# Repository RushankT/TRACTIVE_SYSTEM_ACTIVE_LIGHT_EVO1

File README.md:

# TRACTIVE_SYSTEM_ACTIVE_LIGHT_EVO1

## Overview

This repository contains the finalized KiCad schematic design for the **Tractive System Active Light (TSAL)** circuit, developed for our Formula Student Electric Vehicle project. The TSAL is a critical safety component used to indicate the presence of high voltage in the tractive system when the vehicle is powered on.

## Project Details

- **Project Name**: TSAL Final Design
- **Team**: Zuura Formula Racing
- **Engineer**: Rushank Talwar, EV Powertrain Lead
- **Tool Used**: KiCad (Recommended version: 6.x or newer)
- **Date**: July 2025

## Functionality

The TSAL circuit complies with Formula Student Electric rules and includes:
- A high-brightness red LED indicator visible from 3 meters.
- Blinking at ≥ 1 Hz when TS voltage > 60 VDC.
- Green Light Turns on when TS voltage < 60 VDC.
- Isolation and safety using optocouplers and fail-safe design.
- Powered by a reliable low-voltage source (e.g., 12V DC).

## File Structure

- `TSAL_final.kicad_sch`: Main schematic file for the TSAL circuit.
- (Optional) Future files: `TSAL_final.kicad_pcb`, BOM, gerber files.

## Relevant Rules

EV4.10 Tractive System Active Light

EV4.10.1 The vehicles must include a single TSAL that must indicate the TS status. The TSAL must
not perform any other functions. A TSAL with multiple LEDs in one housing is allowed.

EV4.10.2 The TSAL itself must have a red light, flashing continuously with a frequency between 2 Hz
and 5 Hz and a duty cycle of 50%, active if and only if the LVS is active and the voltage
across any DC-link capacitor exceeds
• 60VDC or 50VACRMS
• Half the nominal TS voltage
whichever is lower.

EV4.10.3 The TSAL itself must have a green light, continuously on, active if and only if the LVS is
active and ALL of the following conditions are true:
• All AIRs are opened.
• The pre-charge relay, see EV5.7.2, is opened.
• The voltage at the vehicle side of the AIRs inside the TSAC does not exceed 60VDC
or 50VACRMS.

EV4.10.4 The mentioned voltage detection must be performed inside the respective TS enclosure.

EV4.10.5 The mentioned states of the relays (opened/closed) are the actual mechanical states. The
mechanical state can differ from the intentional state, i.e. if a relay is stuck. Any circuitry
detecting the mechanical state must meet EV5.6.2.

EV4.10.6 The voltage detection circuit of the red light and the relay state and voltage detection circuit
of the green light must be independent. Any plausibility check between both lights is not
allowed. A TSAL state with both lights simultaneously active might occur and must not be
prevented.

EV4.10.7 The TSAL must:
• Be located lower than the highest point of the main hoop and including the mounting
within the rollover protection envelope, see T1.1.15.
• Be no lower than 75mm from the highest point of the main hoop.
• Not be able to contact the driver’s helmet in any circumstances.

EV4.10.8 The entire illuminated surface of the TSAL must be clearly visible:
• Except for angles less than 10° which are blocked by the main hoop.
• From a point 1:60m vertically from ground level, within 3m horizontal radius from
the TSAL.
• In direct sunlight.

EV4.10.9 The TSAL and all needed circuitry must be hard-wired electronics. Software control is not
permitted.

EV4.10.10 A green indicator light in the cockpit that is easily visible even in bright sunlight and clearly
marked with “TS off” must light up if TSAL green light is on, see EV4.10.3.

EV4.10.11 Signals influencing the TSAL and the indicator according to EV4.10.10 are SCS, see T11.9.
The individual safe state of each of the TSAL lights is off. The TSAL has an active indication
of the absence of failures (continuous green illumination) and thus the red light must not be
illuminated for a visible check, see T11.9.5.

EV4.10.12 The TSAL’s red light voltage detection circuit, see EV4.10.2, does not need to detect an
open circuit, as required by T11.9, when no voltage is present. A plausibility check must not
be implemented.

EV4.10.13 The TSAL’s green light relay state detection circuit, see EV4.10.3, does not need to detect an
open circuit, as required by T11.9, when the intentional state of the used (auxiliary) contact
is opened. A plausibility check using the intentional relay state must be implemented in a
way that the TSAL’s green light stays off after the open circuit is detectable.

EV4.10.14 The TSAL’s green light voltage detection circuit, see EV4.10.3, does not need to detect an
open circuit, as required by T11.9, when no voltage is present. A plausibility check using
the intentional relay states must be implemented in a way that the TSAL’s green light stays
off after the open circuit of the accumulator voltage detection circuit is detectable.

EV4.10.15 The latching required by EV4.10.13 and EV4.10.14 must not be triggered during normal
operation conditions and must only be reset by power cycling the LVS.

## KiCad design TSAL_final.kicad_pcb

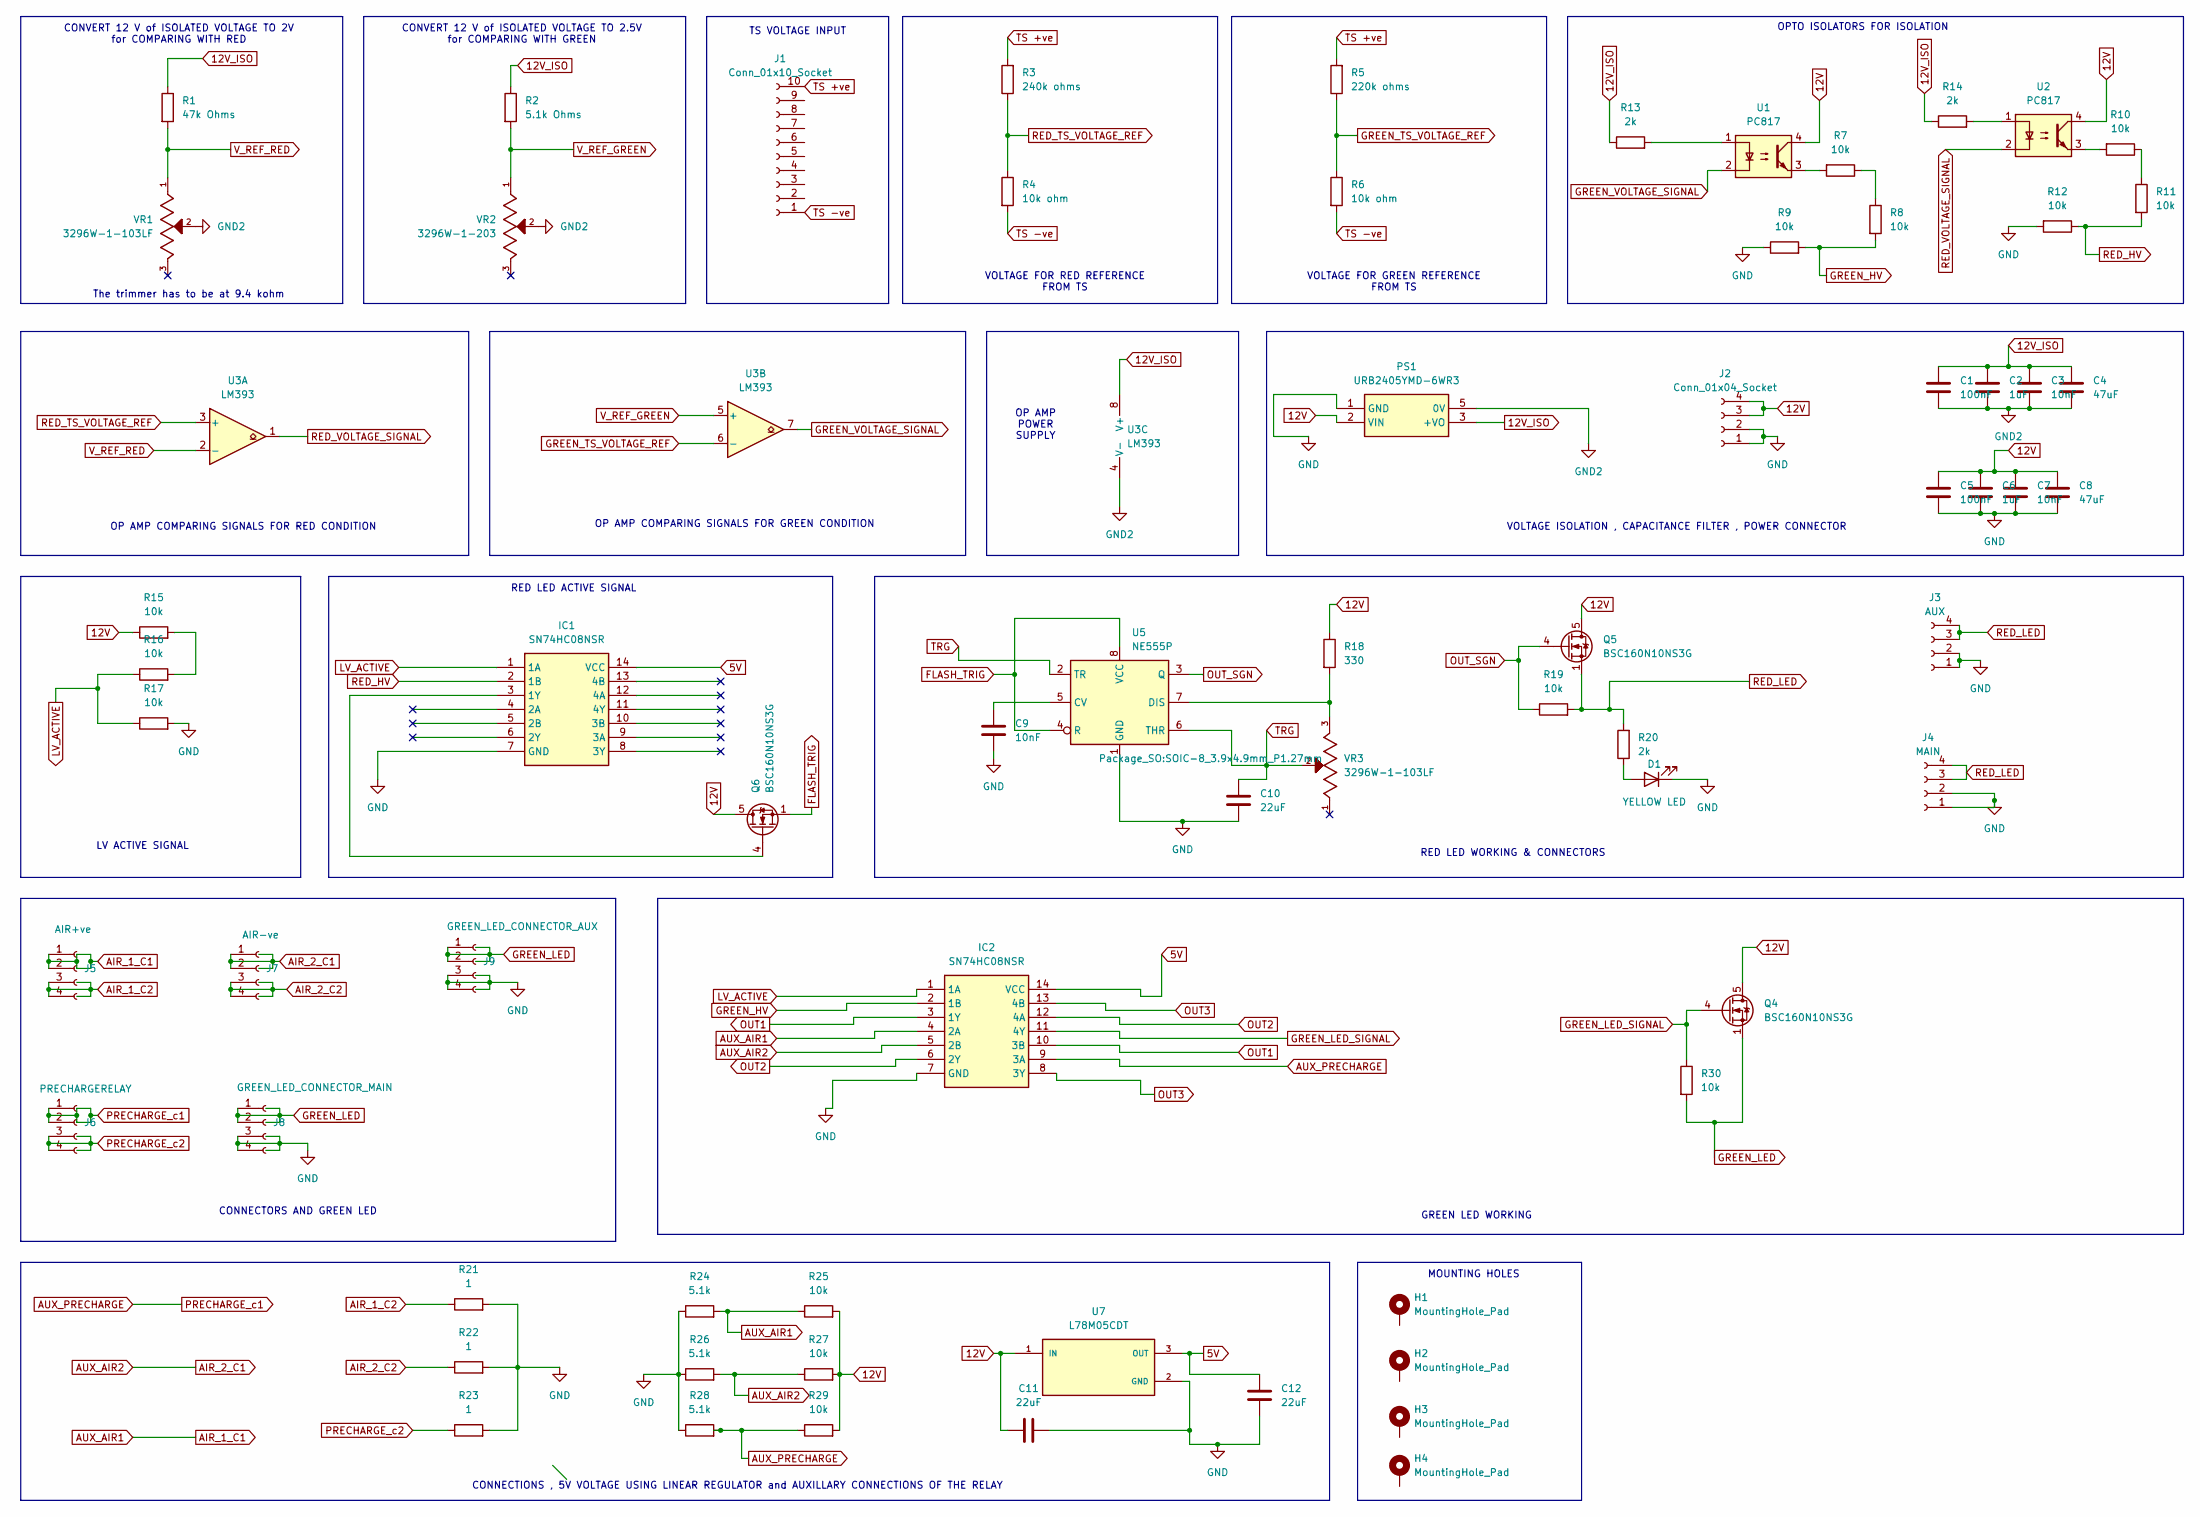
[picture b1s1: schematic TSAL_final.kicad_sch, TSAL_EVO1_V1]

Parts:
C1, C5: 100nF; C_0805_2012Metric_Pad1.18x1.45mm_HandSolder
C2, C6: 1uF; C_0805_2012Metric_Pad1.18x1.45mm_HandSolder
C3, C7, C9: 10nF; C_0805_2012Metric_Pad1.18x1.45mm_HandSolder
C4, C8: 47uF; C_0805_2012Metric_Pad1.18x1.45mm_HandSolder
C10, C11, C12: 22uF; C_0805_2012Metric_Pad1.18x1.45mm_HandSolder
D1: YELLOW LED; LED_0805_2012Metric_Pad1.15x1.40mm_HandSolder
H1, H2, H3, H4: MountingHole_Pad; MountingHole_4.3mm_M4_ISO7380_Pad_TopBottom
IC1, IC2: SN74HC08NSR; SOIC127P780X200-14N; Mouser Part Number 595-SN74HC08NSR
J1: Conn_01x10_Socket; JST_VH_B10P-VH-B_1x10_P3.96mm_Vertical
J2: Conn_01x04_Socket; JST_VH_B4P-VH-B_1x04_P3.96mm_Vertical
J3: AUX; JST_VH_B4P-VH-B_1x04_P3.96mm_Vertical
J4: MAIN; JST_VH_B4P-VH-B_1x04_P3.96mm_Vertical
J5: AIR+ve; JST_VH_B4P-VH-B_1x04_P3.96mm_Vertical
J6: PRECHARGERELAY; JST_VH_B4P-VH-B_1x04_P3.96mm_Vertical
J7: AIR-ve; JST_VH_B4P-VH-B_1x04_P3.96mm_Vertical
J8: GREEN_LED_CONNECTOR_MAIN; JST_VH_B4P-VH-B_1x04_P3.96mm_Vertical
J9: GREEN_LED_CONNECTOR_AUX; JST_VH_B4P-VH-B_1x04_P3.96mm_Vertical
PS1: URB2405YMD-6WR3; URB2405YMD6WR3; Manufacturer_Part_Number URB2405YMD-6WR3
Q4, Q5, Q6: BSC160N10NS3G; TDSON-8-1
R1: 47k Ohms; R_0805_2012Metric_Pad1.20x1.40mm_HandSolder
R2: 5.1k Ohms; R_0805_2012Metric_Pad1.20x1.40mm_HandSolder
R3: 240k ohms; R_2512_6332Metric_Pad1.40x3.35mm_HandSolder
R4, R6: 10k ohm; R_2512_6332Metric_Pad1.40x3.35mm_HandSolder
R5: 220k ohms; R_2512_6332Metric_Pad1.40x3.35mm_HandSolder
R7, R8, R9, R10, R11, R12, R15, R16, R17, R19, R25, R27, R29, R30: 10k; R_0805_2012Metric_Pad1.20x1.40mm_HandSolder
R13, R14, R20: 2k; R_0805_2012Metric_Pad1.20x1.40mm_HandSolder
R18: 330; R_0805_2012Metric_Pad1.20x1.40mm_HandSolder
R21, R22, R23: 1; R_0805_2012Metric_Pad1.20x1.40mm_HandSolder
R24, R26, R28: 5.1k; R_0805_2012Metric_Pad1.20x1.40mm_HandSolder
U1, U2: PC817; DIP-4_W7.62mm
U3: LM393; SO08
U5: NE555P; SOIC-8_3.9x4.9mm_P1.27mm
U7: L78M05CDT; VREG_L78M05CDT; PARTREV 24
VR1, VR3: 3296W-1-103LF; TRIM_3296W-1-103LF; PARTREV 05/16
VR2: 3296W-1-203; TRIM_3296W-1-203; PARTREV 05/16

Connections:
5V: C12.2, IC1.14 (VCC), IC2.14 (VCC), U7.3 (OUT)
12V: C5.1, C6.1, C7.1, C8.1, C11.1, J2.3, J2.4, PS1.2 (VIN), Q4.5 (D), Q5.5 (D), Q6.5 (D), R15.1, R18.1, R25.2, R27.2, R29.2, U1.4, U2.4, U7.1 (IN)
12V_ISO: C1.1, C2.1, C3.1, C4.1, PS1.3 (+VO), R1.1, R2.1, R13.1, R14.1, U3.8 (V+)
AIR_1_C1: IC2.4 (2A), J5.1, J5.2, R24.2, R25.1
AIR_1_C2: J5.3, J5.4, R21.1
AIR_2_C1: IC2.5 (2B), J7.1, J7.2, R26.2, R27.1
AIR_2_C2: J7.3, J7.4, R22.1
AUX_PRECHARGE: IC2.9 (3A), J6.1, J6.2, R28.2, R29.1
FLASH_TRIG: Q6.1 (S), Q6.2 (S), Q6.3 (S), U5.4 (R), U5.8 (VCC)
GND: C5.2, C6.2, C7.2, C8.2, C9.2, C10.2, C11.2, C12.1, D1.1 (K), IC1.7 (GND), IC2.7 (GND), J2.1, J2.2, J3.1, J3.2, J4.1, J4.2, J8.3, J8.4, J9.3, J9.4, PS1.1 (GND), R9.1, R12.2, R17.2, R21.2, R22.2, R23.2, R24.1, R26.1, R28.1, U5.1 (GND), U7.2 (GND)
GND2: C1.2, C2.2, C3.2, C4.2, PS1.5 (0V), U3.4 (V-), VR1.2, VR2.2
GREEN_HV: IC2.2 (1B), R8.2, R9.2
GREEN_LED: J8.1, J8.2, J9.1, J9.2, Q4.1 (S), Q4.2 (S), Q4.3 (S), R30.2
GREEN_LED_SIGNAL: IC2.11 (4Y), Q4.4 (G), R30.1
GREEN_TS_VOLTAGE_REF: R5.1, R6.1, U3.6 (-)
GREEN_VOLTAGE_SIGNAL: U1.2, U3.7
LV_ACTIVE: IC1.1 (1A), IC2.1 (1A), R16.1, R17.1
unnamed: D1.2 (A), R20.1
unnamed: IC1.3 (1Y), Q6.4 (G)
unnamed: R7.1, R8.1
unnamed: R7.2, U1.3
unnamed: R10.1, R11.1
unnamed: R10.2, U2.3
unnamed: R13.2, U1.1
unnamed: R14.2, U2.1
unnamed: R15.2, R16.2
unnamed: C9.1, U5.5 (CV)
unnamed: R18.2, U5.7 (DIS), VR3.3
OUT1: IC2.3 (1Y), IC2.10 (3B)
OUT2: IC2.6 (2Y), IC2.12 (4A)
OUT3: IC2.8 (3Y), IC2.13 (4B)
OUT_SGN: Q5.4 (G), R19.1, U5.3 (Q)
PRECHARGE_c2: J6.3, J6.4, R23.1
RED_HV: IC1.2 (1B), R11.2, R12.1
RED_LED: J3.3, J3.4, J4.3, J4.4, Q5.1 (S), Q5.2 (S), Q5.3 (S), R19.2, R20.2
RED_TS_VOLTAGE_REF: R3.1, R4.1, U3.3 (+)
RED_VOLTAGE_SIGNAL: U2.2, U3.1
TRG: C10.1, U5.2 (TR), U5.6 (THR), VR3.2
TS +ve: J1.10, R3.2, R5.2
TS -ve: J1.1, R4.2, R6.2
V_REF_GREEN: R2.2, U3.5 (+), VR2.1
V_REF_RED: R1.2, U3.2 (-), VR1.1

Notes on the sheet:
OPTO ISOLATORS FOR ISOLATION
VOLTAGE FOR RED REFERENCE FROM TS
TS VOLTAGE INPUT
VOLTAGE FOR GREEN REFERENCE FROM TS
OP AMP COMPARING SIGNALS FOR GREEN CONDITION
CONVERT 12 V of ISOLATED VOLTAGE TO 2V for COMPARING WITH RED
GREEN LED WORKING
CONNECTIONS , 5V VOLTAGE USING LINEAR REGULATOR and AUXILLARY CONNECTIONS OF THE RELAY
VOLTAGE ISOLATION , CAPACITANCE FILTER , POWER CONNECTOR
RED LED ACTIVE SIGNAL
LV ACTIVE SIGNAL
MOUNTING HOLES
OP AMP POWER SUPPLY
CONVERT 12 V of ISOLATED VOLTAGE TO 2.5V for COMPARING WITH GREEN
RED LED WORKING & CONNECTORS
The trimmer has to be at 9.4 kohm
OP AMP COMPARING SIGNALS FOR RED CONDITION
CONNECTORS AND GREEN LED

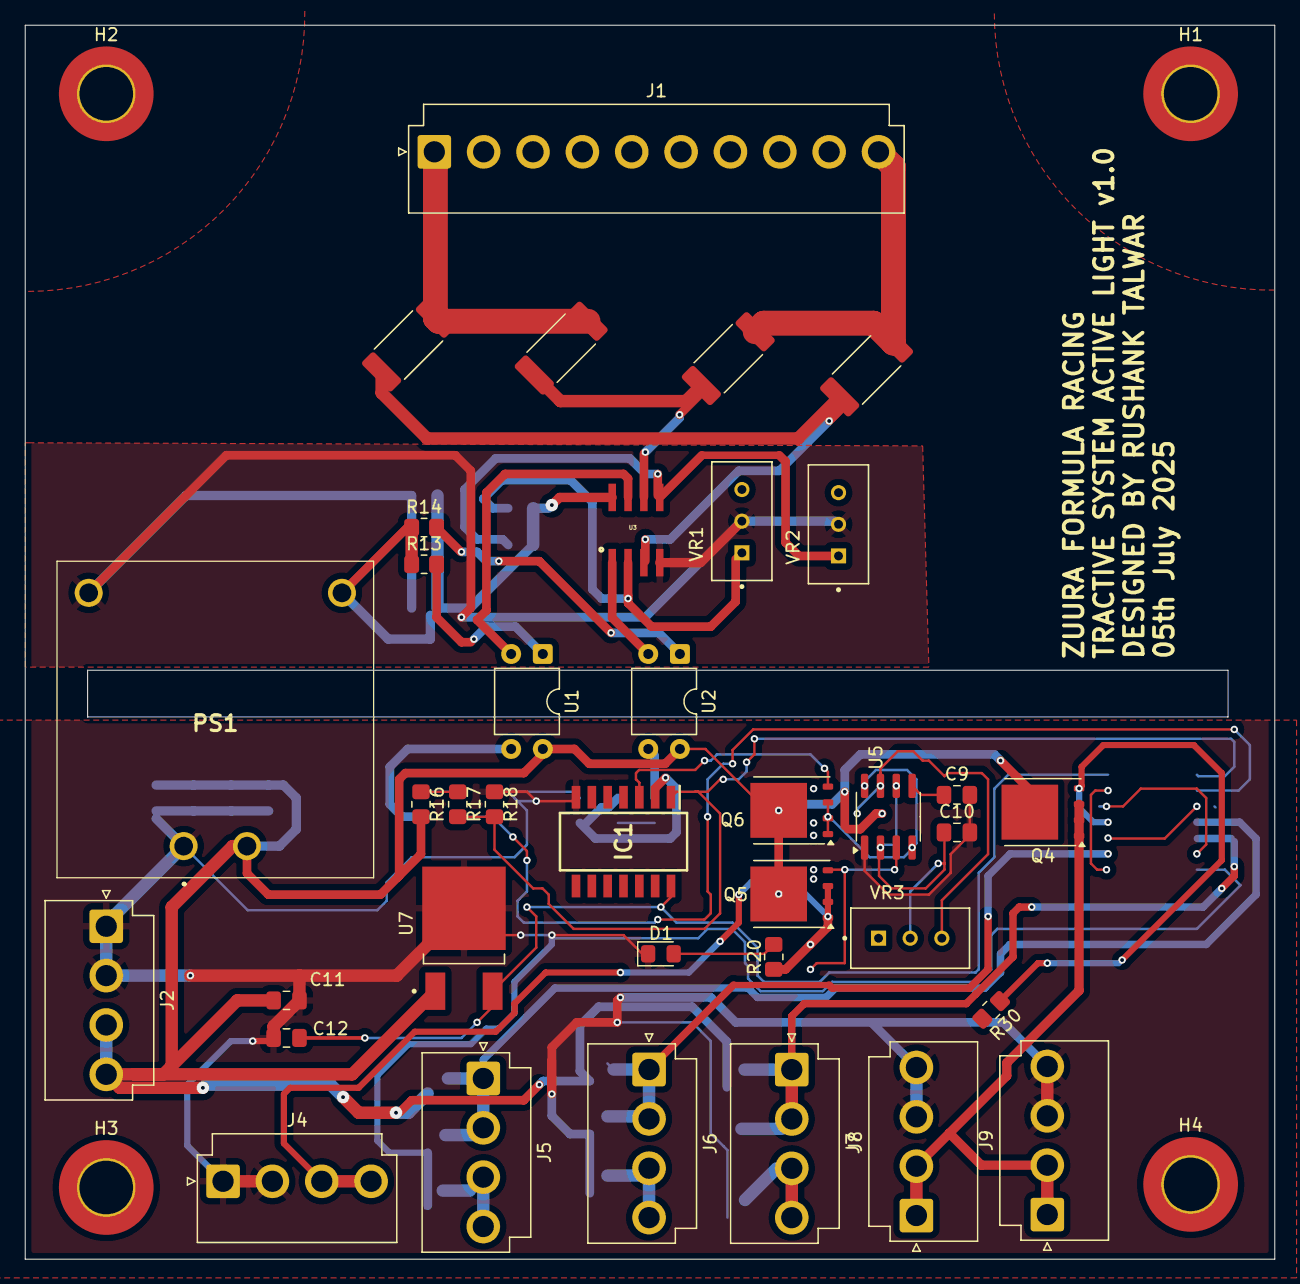
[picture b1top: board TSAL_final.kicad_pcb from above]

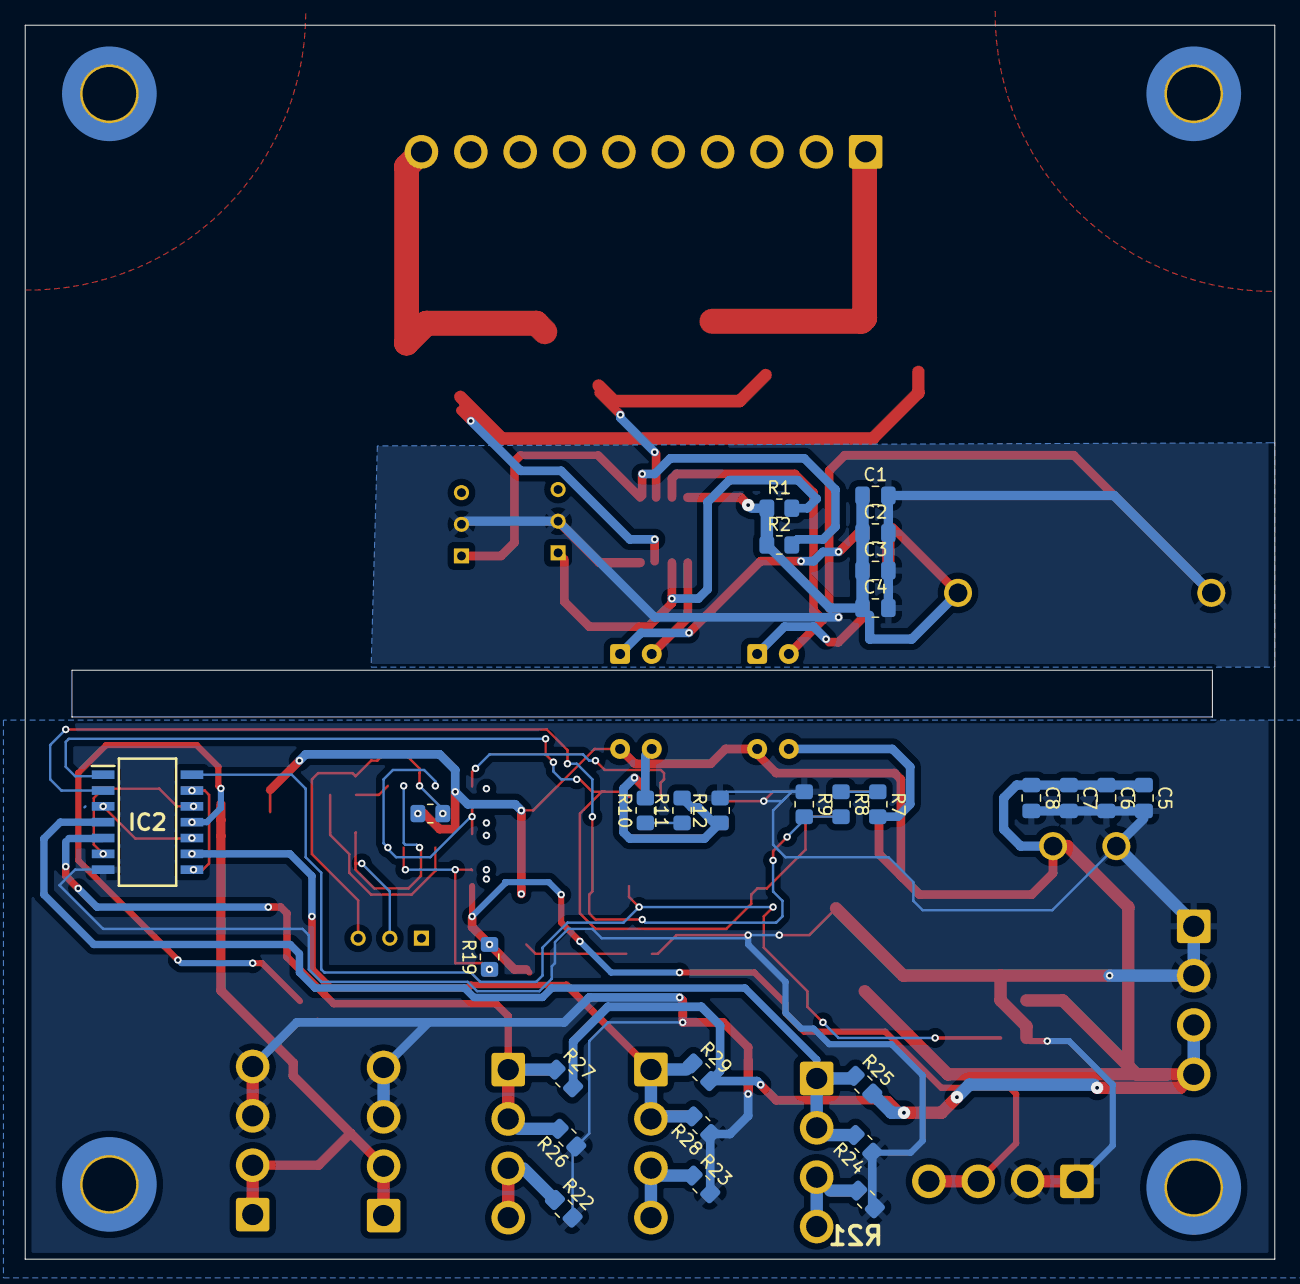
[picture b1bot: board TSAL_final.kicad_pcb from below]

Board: 2 copper layers, 100.2 x 99.0 mm, 69 parts (28 on the bottom side), 42 nets.
